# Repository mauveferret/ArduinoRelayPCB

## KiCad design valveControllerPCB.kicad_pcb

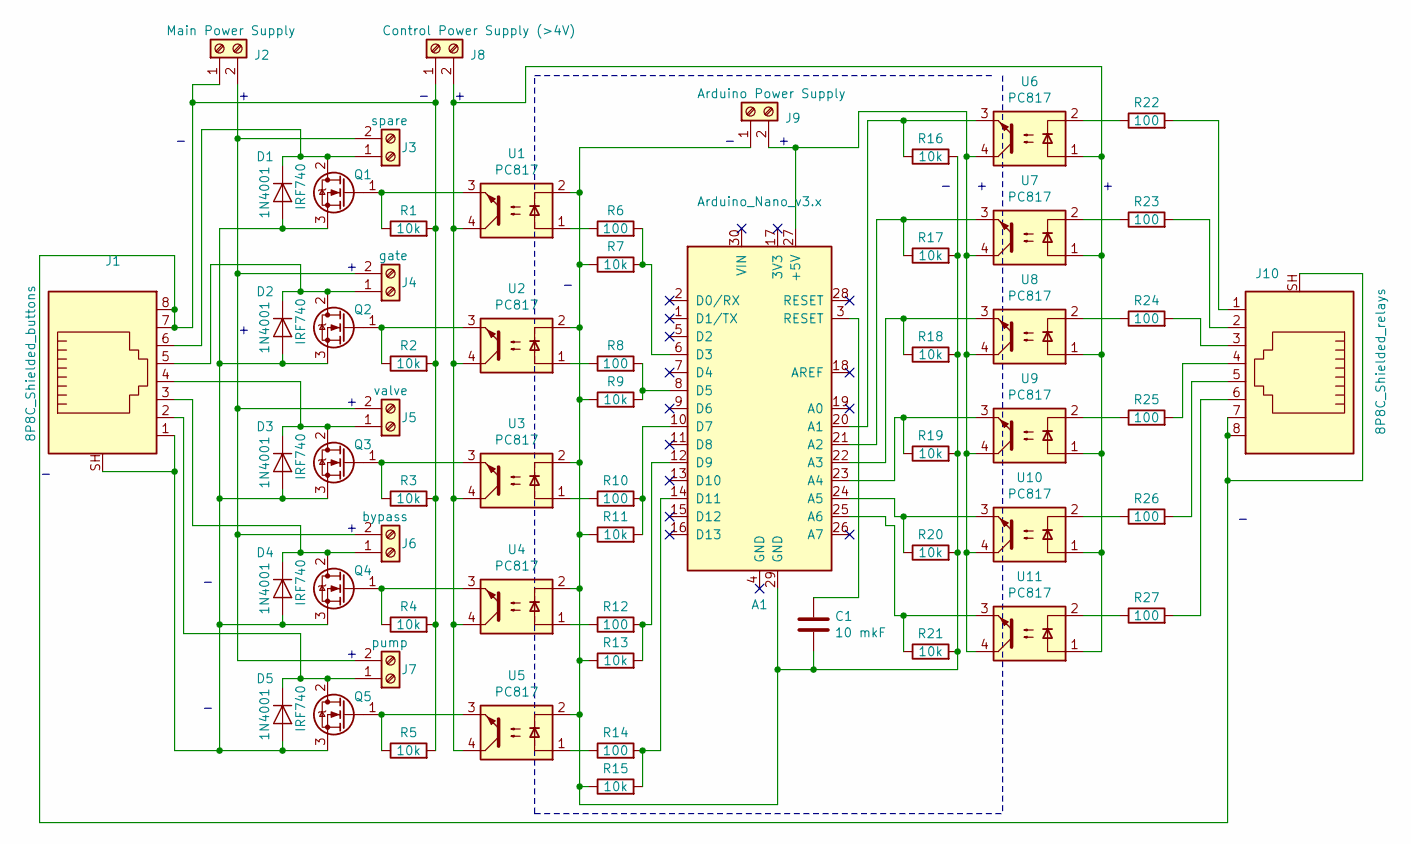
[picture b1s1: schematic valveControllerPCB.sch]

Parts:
A1: Arduino_Nano_v3.x; Arduino_Nano
C1: 10 mkF; CP_Radial_D5.0mm_P2.50mm
D1, D2, D3, D4, D5: 1N4001; D_DO-41_SOD81_P7.62mm_Horizontal
J1: 8P8C_Shielded_buttons; RJ45_Amphenol_RJHSE5380
J2: Main Power Supply; Altech_AK300_1x02_P5.00mm_45-Degree
J3: spare; Altech_AK300_1x02_P5.00mm_45-Degree
J4: gate; Altech_AK300_1x02_P5.00mm_45-Degree
J5: valve; Altech_AK300_1x02_P5.00mm_45-Degree
J6: bypass; Altech_AK300_1x02_P5.00mm_45-Degree
J7: pump; Altech_AK300_1x02_P5.00mm_45-Degree
J8: Control Power Supply (>4V); Altech_AK300_1x02_P5.00mm_45-Degree
J9: Arduino Power Supply; Altech_AK300_1x02_P5.00mm_45-Degree
J10: 8P8C_Shielded_relays; RJ45_Amphenol_RJHSE5380
Q1, Q2, Q3, Q4, Q5: IRF740; TO-220-3_Vertical
R1, R2, R3, R4, R5, R7, R9, R11, R13, R15, R16, R17, R18, R19, R20, R21: 10k; R_Axial_DIN0309_L9.0mm_D3.2mm_P12.70mm_Horizontal
R6, R8, R10, R12, R14, R22, R23, R24, R25, R26, R27: 100; R_Axial_DIN0207_L6.3mm_D2.5mm_P10.16mm_Horizontal
U1, U2, U3, U4, U5, U6, U7, U8, U9, U10, U11: PC817; DIP-4_W7.62mm

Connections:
unnamed: A1.3 (RESET), C1.1
unnamed: A1.6 (D3), R6.2, R7.2
unnamed: A1.8 (D5), R8.2, R9.2
unnamed: A1.10 (D7), R10.2, R11.2
unnamed: A1.12 (D9), R12.2, R13.2
unnamed: A1.14 (D11), R14.2, R15.2
unnamed: A1.20 (A1), R16.1, U6.3
unnamed: A1.21 (A2), R17.1, U7.3
unnamed: A1.22 (A3), R18.1, U8.3
unnamed: A1.23 (A4), R19.1, U9.3
unnamed: A1.24 (A5), R20.1, U10.3
unnamed: A1.25 (A6), R21.1, U11.3
unnamed: A1.27 (+5V), J9.2, U6.4, U7.4, U8.4, U9.4, U10.4, U11.4
unnamed: A1.29 (GND), C1.2, J9.1, R7.1, R9.1, R11.1, R13.1, R15.1, R16.2, R17.2, R18.2, R19.2, R20.2, R21.2, U1.2, U2.2, U3.2, U4.2, U5.2
unnamed: D1.1 (K), J1.6, J3.1, Q1.2 (D)
unnamed: D1.2 (A), D2.2 (A), D3.2 (A), D4.2 (A), D5.2 (A), J1.1, J1.SH, Q1.3 (S), Q2.3 (S), Q3.3 (S), Q4.3 (S), Q5.3 (S)
unnamed: D2.1 (K), J1.5, J4.1, Q2.2 (D)
unnamed: D3.1 (K), J1.4, J5.1, Q3.2 (D)
unnamed: D4.1 (K), J1.3, J6.1, Q4.2 (D)
unnamed: D5.1 (K), J1.2, J7.1, Q5.2 (D)
unnamed: J1.7, J1.8, J2.1, J8.1, J10.7, J10.8, J10.SH, R1.2, R2.2, R3.2, R4.2, R5.2
unnamed: J2.2, J3.2, J4.2, J5.2, J6.2, J7.2
unnamed: J8.2, U1.4, U2.4, U3.4, U4.4, U5.4, U6.1, U7.1, U8.1, U9.1, U10.1, U11.1
unnamed: J10.1, R22.2
unnamed: J10.2, R23.2
unnamed: J10.3, R24.2
unnamed: J10.4, R25.2
unnamed: J10.5, R26.2
unnamed: J10.6, R27.2
unnamed: Q1.1 (G), R1.1, U1.3
unnamed: Q2.1 (G), R2.1, U2.3
unnamed: Q3.1 (G), R3.1, U3.3
unnamed: Q4.1 (G), R4.1, U4.3
unnamed: Q5.1 (G), R5.1, U5.3
unnamed: R6.1, U1.1
unnamed: R8.1, U2.1
unnamed: R10.1, U3.1
unnamed: R12.1, U4.1
unnamed: R14.1, U5.1
unnamed: R22.1, U6.2
unnamed: R23.1, U7.2
unnamed: R24.1, U8.2
unnamed: R25.1, U9.2
unnamed: R26.1, U10.2
unnamed: R27.1, U11.2

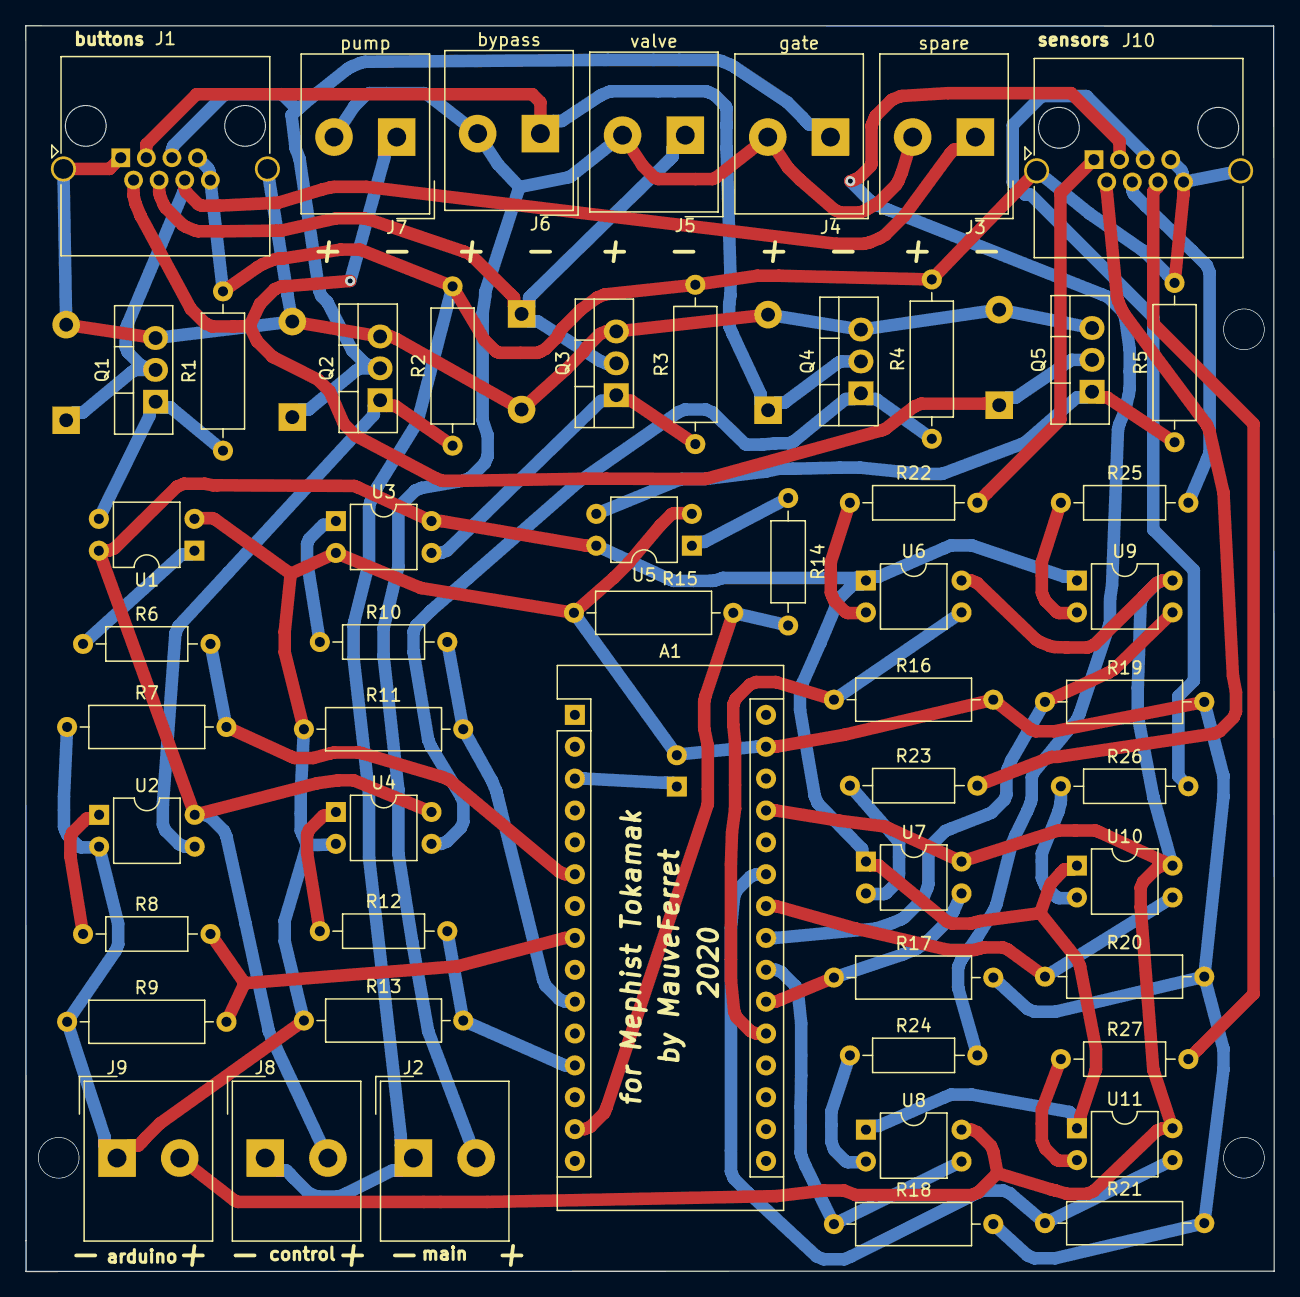
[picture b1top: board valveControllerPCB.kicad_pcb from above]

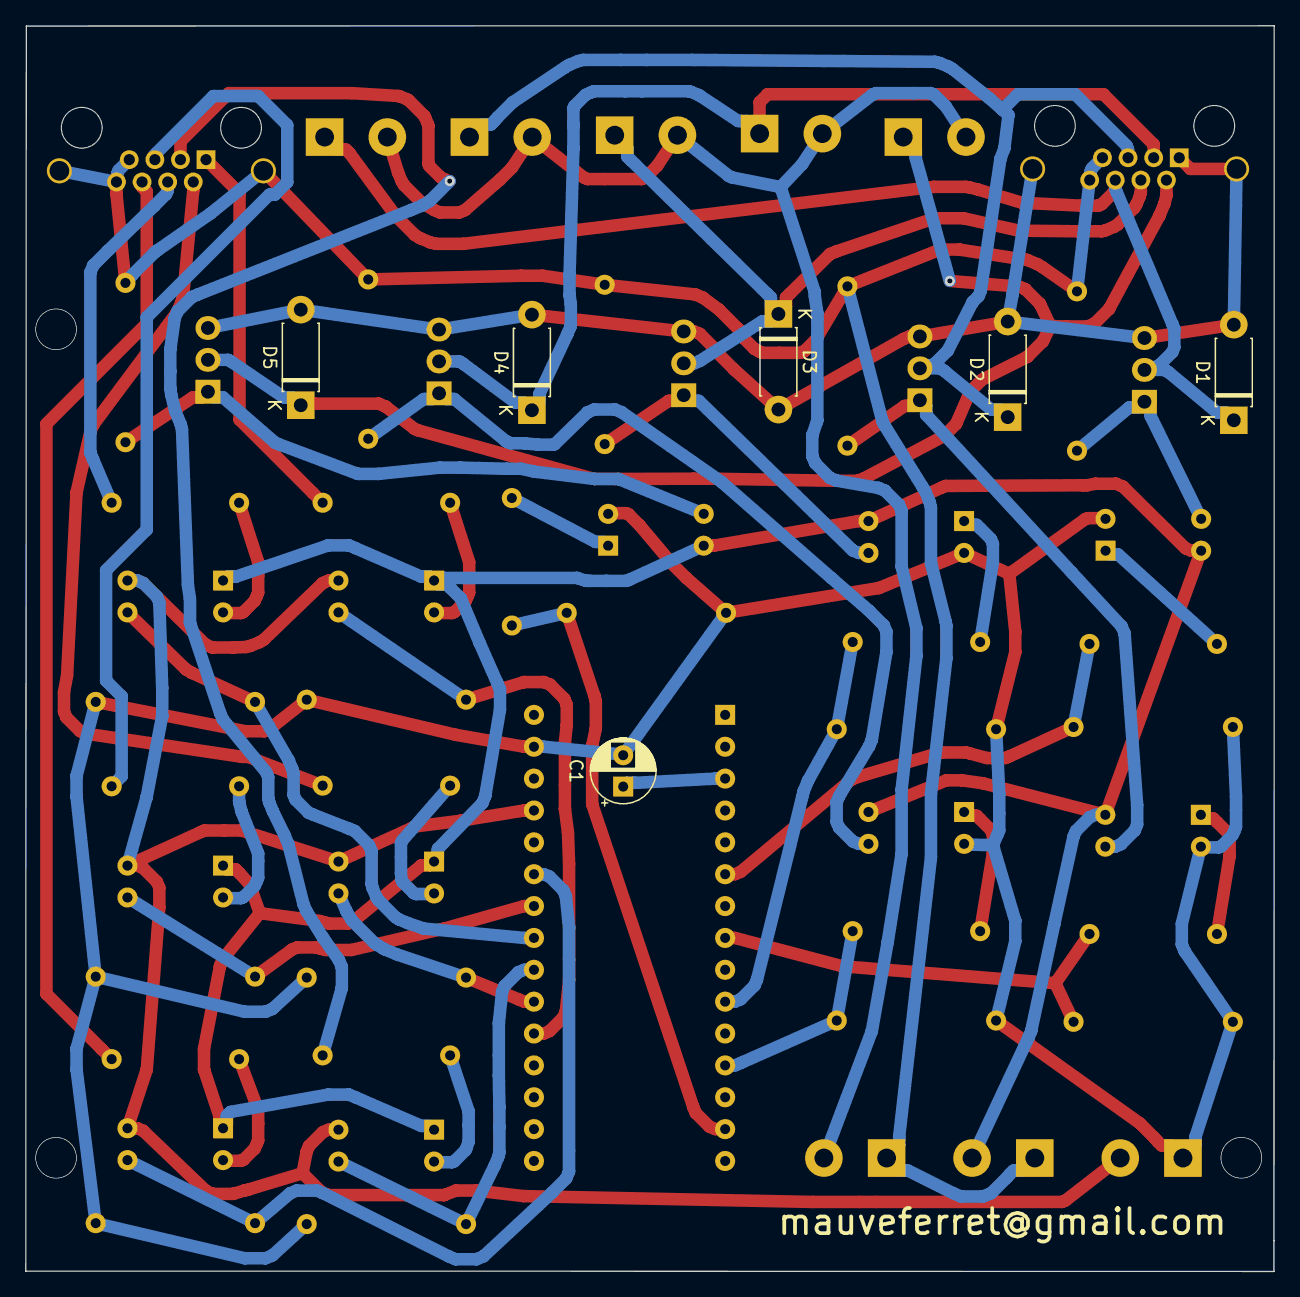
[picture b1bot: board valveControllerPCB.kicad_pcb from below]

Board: 2 copper layers, 99.5 x 99.3 mm, 60 parts (6 on the bottom side), 45 nets.

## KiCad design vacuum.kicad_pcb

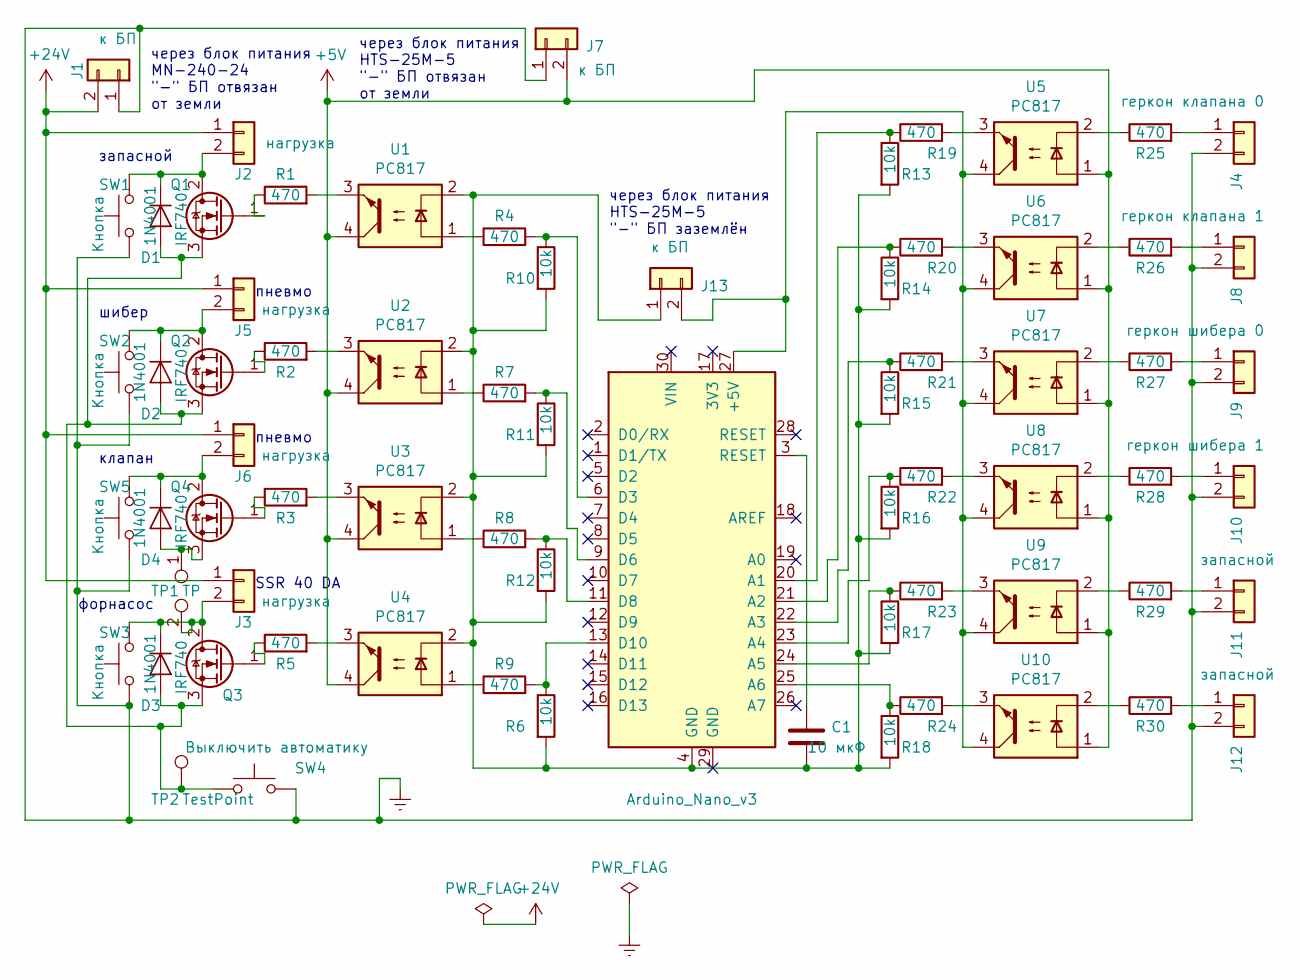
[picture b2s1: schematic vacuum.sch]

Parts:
A1: Arduino_Nano_v3; Arduino_Nano_WithMountingHoles
C1: 10 мкФ; C_Disc_D6.0mm_W2.5mm_P5.00mm
D1, D2, D3, D4: 1N4001; D_DO-41_SOD81_P10.16mm_Horizontal
J1, J7, J13: к БП; Altech_AK300_1x02_P5.00mm_45-Degree
J2, J3, J5, J6: нагрузка; Altech_AK300_1x02_P5.00mm_45-Degree
J4: геркон клапана 0; Altech_AK300_1x02_P5.00mm_45-Degree
J8: геркон клапана 1; Altech_AK300_1x02_P5.00mm_45-Degree
J9: геркон шибера 0; Altech_AK300_1x02_P5.00mm_45-Degree
J10: геркон шибера 1; Altech_AK300_1x02_P5.00mm_45-Degree
J11, J12: запасной; Altech_AK300_1x02_P5.00mm_45-Degree
Q1, Q2, Q3, Q4: IRF740; TO-220-3_Vertical
R1, R2, R3, R4, R7, R8, R9, R19, R20, R21, R22, R23, R24, R25, R26, R27, R28, R29, R30: 470; R_Axial_DIN0207_L6.3mm_D2.5mm_P5.08mm_Vertical
R5: 470; R_Axial_DIN0207_L6.3mm_D2.5mm_P7.62mm_Horizontal
R6, R10, R11, R12, R13, R14, R15, R16, R17, R18: 10k; R_Axial_DIN0309_L9.0mm_D3.2mm_P5.08mm_Vertical
SW1, SW2, SW3, SW5: Кнопка; PinHeader_1x02_P2.54mm_Vertical
SW4: Выключить автоматику; Altech_AK300_1x02_P5.00mm_45-Degree
TP1: TP; PinHeader_1x02_P2.54mm_Vertical
TP2: TestPoint; PinHeader_1x01_P2.54mm_Vertical
U1, U2, U3, U4, U5, U6, U7, U8, U9, U10: PC817; DIP-4_W7.62mm

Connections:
+5V: J7.2, U1.4, U2.4, U3.4, U4.4, U5.1, U6.1, U7.1, U8.1, U9.1, U10.1
+24V: J1.2, J2.1, J3.1, J5.1, J6.1
Earth: J1.1, J4.2, J7.1, J8.2, J9.2, J10.2, J11.2, J12.2, SW1.1, SW2.1, SW3.1, SW4.2, SW5.1
unnamed: A1.3 (RESET), C1.1
unnamed: A1.4 (GND), C1.2, J13.1, R6.2, R10.2, R11.2, R12.2, R13.2, R14.2, R15.2, R16.2, R17.2, R18.2, U1.2, U2.2, U3.2, U4.2
unnamed: A1.6 (D3), R4.2, R10.1
unnamed: A1.9 (D6), R7.2, R11.1
unnamed: A1.11 (D8), R8.2, R12.1
unnamed: A1.13 (D10), R6.1, R9.2
unnamed: A1.20 (A1), R13.1, R19.1
unnamed: A1.21 (A2), R14.1, R20.1
unnamed: A1.22 (A3), R15.1, R21.1
unnamed: A1.23 (A4), R16.1, R22.1
unnamed: A1.24 (A5), R17.1, R23.1
unnamed: A1.25 (A6), R18.1, R24.1
unnamed: A1.27 (+5V), J13.2, U5.4, U6.4, U7.4, U8.4, U9.4, U10.4
unnamed: D1.1 (K), J2.2, Q1.2 (D), SW1.2
unnamed: D1.2 (A), D2.2 (A), D3.2 (A), Q1.3 (S), Q2.3 (S), Q3.3 (S), SW4.1, TP2.1
unnamed: D2.1 (K), J5.2, Q2.2 (D), SW2.2
unnamed: D3.1 (K), J3.2, Q3.2 (D), SW3.2, TP1.2
unnamed: D4.1 (K), J6.2, Q4.2 (D), SW5.2
unnamed: D4.2 (A), Q4.3 (S), TP1.1
unnamed: J4.1, R25.2
unnamed: J8.1, R26.2
unnamed: J9.1, R27.2
unnamed: J10.1, R28.2
unnamed: J11.1, R29.2
unnamed: J12.1, R30.2
unnamed: Q1.1 (G), R1.1
unnamed: Q2.1 (G), R2.1
unnamed: Q3.1 (G), R5.1
unnamed: Q4.1 (G), R3.1
unnamed: R1.2, U1.3
unnamed: R2.2, U2.3
unnamed: R3.2, U3.3
unnamed: R4.1, U1.1
unnamed: R5.2, U4.3
unnamed: R7.1, U2.1
unnamed: R8.1, U3.1
unnamed: R9.1, U4.1
unnamed: R19.2, U5.3
unnamed: R20.2, U6.3
unnamed: R21.2, U7.3
unnamed: R22.2, U8.3
unnamed: R23.2, U9.3
unnamed: R24.2, U10.3
unnamed: R25.1, U5.2
unnamed: R26.1, U6.2
unnamed: R27.1, U7.2
unnamed: R28.1, U8.2
unnamed: R29.1, U9.2
unnamed: R30.1, U10.2

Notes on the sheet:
форнасос
SSR 40 DA
шибер
пневмо
запасной
через блок питания HTS-25M-5 "-" БП заземлён
через блок питания MN-240-24 "-" БП отвязан от земли
через блок питания HTS-25M-5 "-" БП отвязан от земли
клапан

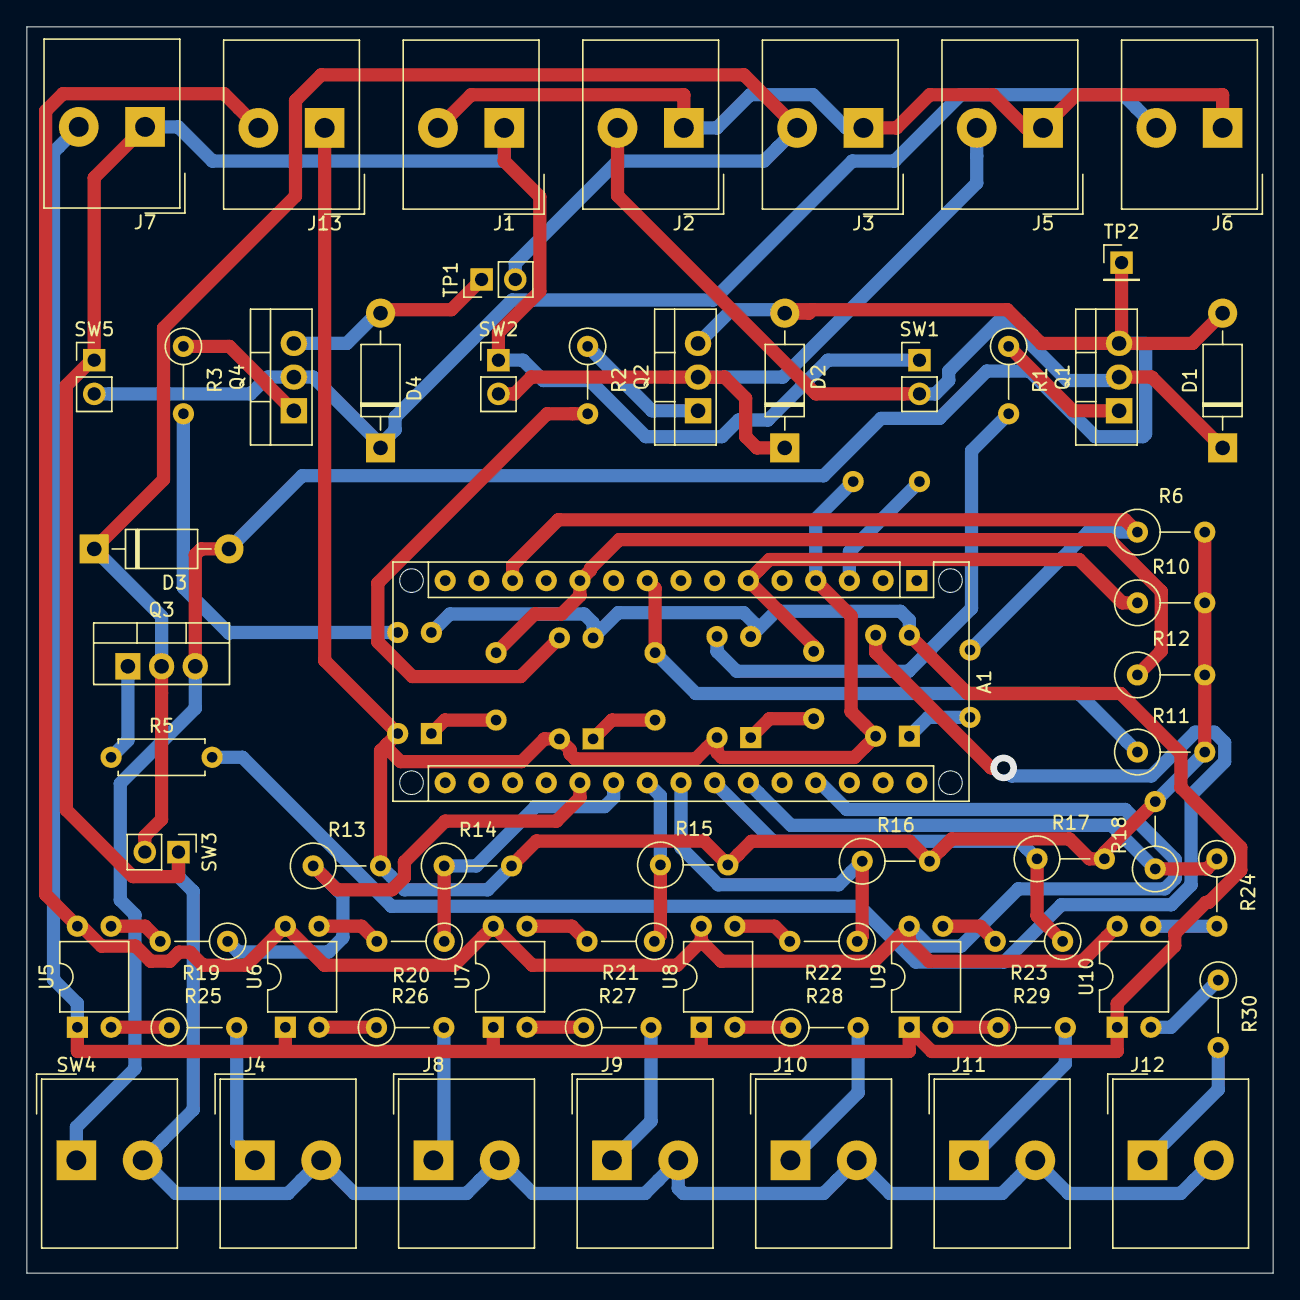
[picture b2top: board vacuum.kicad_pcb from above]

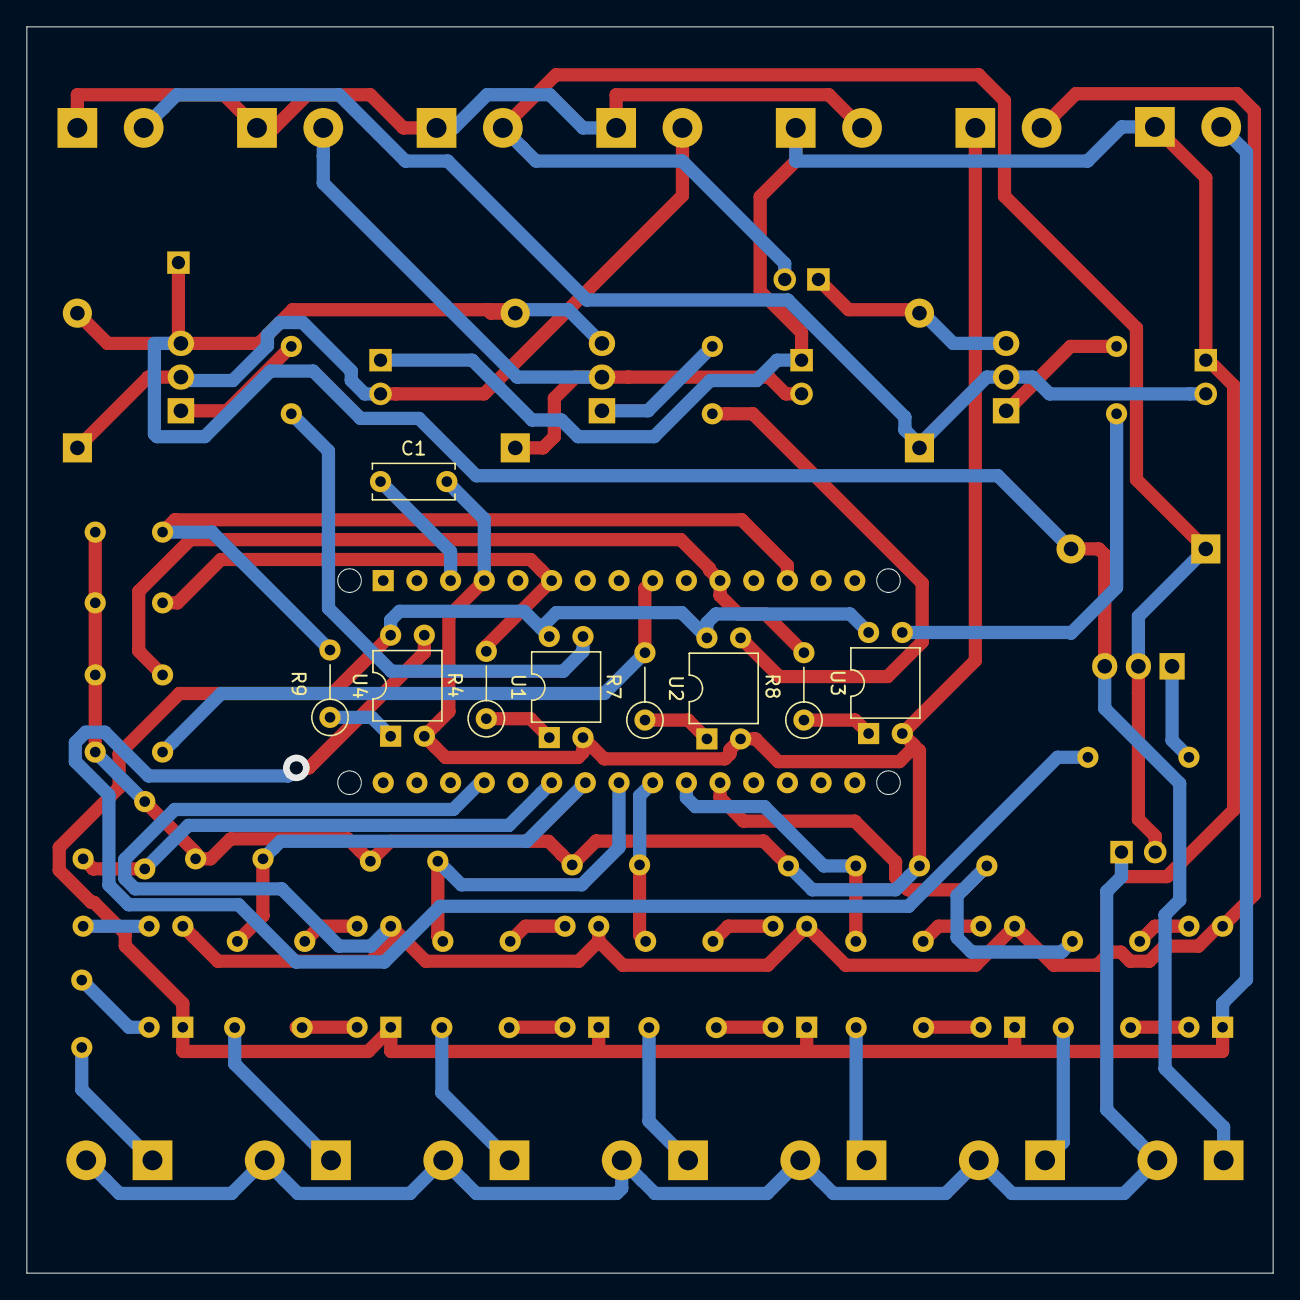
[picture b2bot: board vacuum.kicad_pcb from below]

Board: 2 copper layers, 94.0 x 94.0 mm, 70 parts (9 on the bottom side), 52 nets.

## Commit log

2019-07-13 first version (for presentation)
2019-07-13 License added
2019-07-14 OPTRON added to valves and pump
2019-07-14 OPTRON added to the reed switches, some reserve relay and reed switches added
2019-07-14 common - for power supply added, terminals to power supply added
2019-07-14 some connectors for power supply added
2019-07-14 some scheme bags removed
2019-07-14 some important bags in *.sch removed, PCB partially created
2019-07-14 some bags was removed from scheme, mosfet and optrons was added to PCB, watch new txt doc with some pieces of advice
2019-07-20 vertical resistors aded
2019-07-21 PCB upgrated
2019-07-22 some pins added, PCB upgrated, it seems to be ready for production
2019-07-22 edge added to the PCB
2019-07-23 capasitor added to reset pin of Arduino dor DTR disabling
2019-07-24 diods direction changed to correct
2020-07-07 FULL rebuilt of the scheme, RJ-45 is omplemented, seems to be FINAL version, soon will be tested, wait for the report
